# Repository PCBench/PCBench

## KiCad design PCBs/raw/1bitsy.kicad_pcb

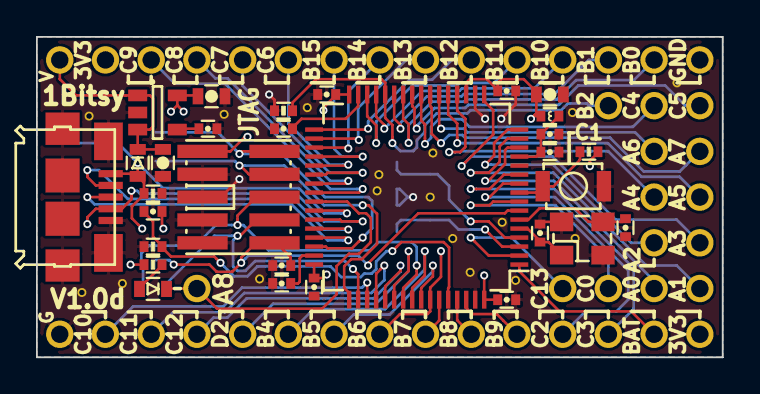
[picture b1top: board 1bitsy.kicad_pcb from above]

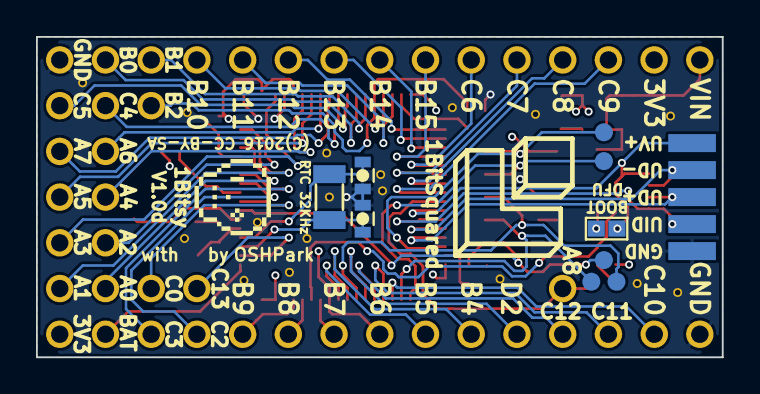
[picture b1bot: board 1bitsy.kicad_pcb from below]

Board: 2 copper layers, 38.1 x 17.8 mm, 88 parts (14 on the bottom side), 63 nets.

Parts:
C1, C5, C13: 4u7; C_0603
C2, C15: 1u; C_0402
C3: 470p; C_0402
C4, C10, C11, C12, C14, C18: 100n; C_0402
C6, C7: 10p; C_0603
C8, C9: 10p; C_0402
C16, C17: 2u2; C_0402
D1: >100mA; D_0603
J1: BOOT; J_0603
L1: 600 Ferrite; L_0402
LED1: ORA; D_0603
P1, P2, P3, P4, P5, P6, P7, P8, P9, P10, P11, P12, P13, P14, P15, P16, P17, P18, P19, P20, P21, P22, P23, P25, P26, P27, P28, P29, P30, P31, P32, P33, P34, P35, P36, P37, P38, P39, P40, P41, P42, P53, P54, P55: CONN_01X01; Pin_Header_Straight_Round_1x01
P24: USB_OTG; Connector_USB_Micro_B_SMD
P43, P44, P45, P46, P47: TP; POGO_PAD_SMD_R_1x1
P48, P49, P50, P51, P52: CONN_01X01; PAD_SMD_1x2.65
R1, R2, R3, R5: 10k; R_0402
R4: 300; R_0402
SW1: TACT; Tact_Switch_Top_B3U-1000P
U1: VREG_3V3; SOT-23-5
U2: STM32F415RGT; LQFP-64_10x10mm_Pitch0.5mm
X1: 32.768kHz; ABS07
X2: 25MHz; ABM8
X3: JTAG-10; FTSH-105-XX-X-DV

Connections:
+3V3: C5.1, C10.1, C11.1, C12.1, C13.1, C14.1, L1.1, P42.1, P54.1, R4.1, R5.1, U1.5, U2.19, U2.32, U2.48, U2.64, X3.1
/BOOT0: C15.2, R3.1, U2.60
/BUTTON: R5.2, SW1.2, U2.9
/JTAG_RST: C18.1, P47.1, U2.7, X3.10
/JTAG_TCK: P44.1, U2.49, X3.4
/JTAG_TDI: P46.1, U2.50, X3.8
/JTAG_TDO: P45.1, U2.55, X3.6
/JTAG_TMS: P43.1, U2.46, X3.2
/OSC32_IN: C6.2, U2.3, X1.2
/OSC32_OUT: C7.2, U2.4, X1.1
/OSC_IN: C8.2, U2.5, X2.1
/OSC_OUT: C9.2, U2.6, X2.2
/PA0: P1.1, U2.14
/PA1: P2.1, U2.15
/PA2: P3.1, U2.16
/PA3: P4.1, U2.17
/PA4: P5.1, U2.20
/PA5: P6.1, U2.21
/PA6: P7.1, U2.22
/PA7: P8.1, U2.23
/PA8: LED1.C, P9.1, U2.41
/PB0: P25.1, U2.26
/PB1: P26.1, U2.27
/PB2: P27.1, R2.1, U2.28
/PB4: P28.1, U2.56
/PB5: P29.1, U2.57
/PB6: P30.1, U2.58
/PB7: P31.1, U2.59
/PB8: P32.1, U2.61
/PB9: P33.1, U2.62
/PB10: P34.1, U2.29
/PB11: P35.1, U2.30
/PB12: P36.1, U2.33
/PB13: P37.1, U2.34
/PB14: P38.1, U2.35
/PB15: P39.1, U2.36
/PC0: P10.1, U2.8
/PC2: P12.1, U2.10
/PC3: P13.1, U2.11
/PC4: P14.1, U2.24
/PC5: P15.1, U2.25
/PC6: P16.1, U2.37
/PC7: P17.1, U2.38
/PC8: P18.1, U2.39
/PC9: P19.1, U2.40
/PC10: P20.1, U2.51
/PC11: P21.1, U2.52
/PC12: P22.1, U2.53
/PC13: P23.1, U2.2
/PD2: P11.1, U2.54
/USB_D+: P24.3, P50.1, U2.45
/USB_D-: P24.2, P49.1, U2.44
/USB_ID: P24.4, P51.1, U2.43
/USB_VBUS: D1.A, J1.1, P24.1, P48.1, R1.1, U2.42
/VBAT: P53.1, U2.1
/VIN: C1.1, D1.C, P40.1, U1.1, U1.3
GND: C1.2, C2.2, C3.2, C4.2, C5.2, C6.1, C7.1, C8.1, C9.1, C10.2, C11.2, C12.2, C13.2, C14.2, C16.2, C17.2, C18.2, P24.5, P24.GND, P41.1, P52.1, P55.1, R1.2, R2.2, R3.2, SW1.1, U1.2, U2.12, U2.18, U2.63, X2.GND, X3.3, X3.5, X3.7, X3.9
unnamed: C2.1, C4.1, L1.2, U2.13
unnamed: C3.1, U1.4
unnamed: C15.1, J1.2
unnamed: C16.1, U2.47
unnamed: C17.1, U2.31
unnamed: LED1.A, R4.2

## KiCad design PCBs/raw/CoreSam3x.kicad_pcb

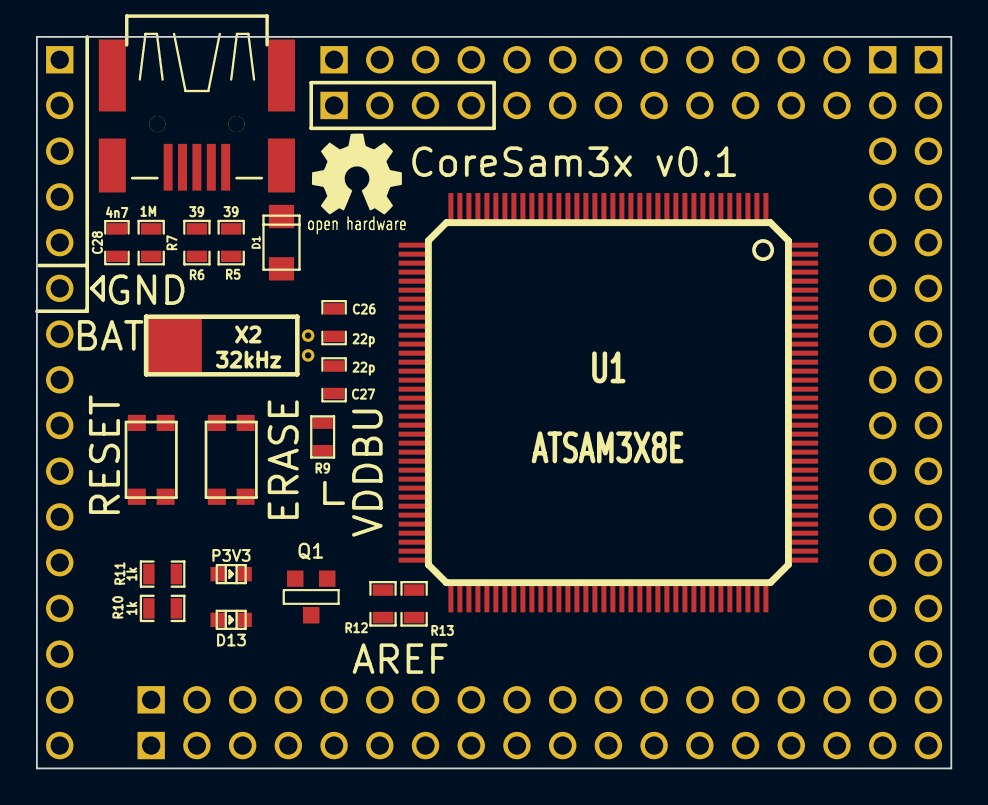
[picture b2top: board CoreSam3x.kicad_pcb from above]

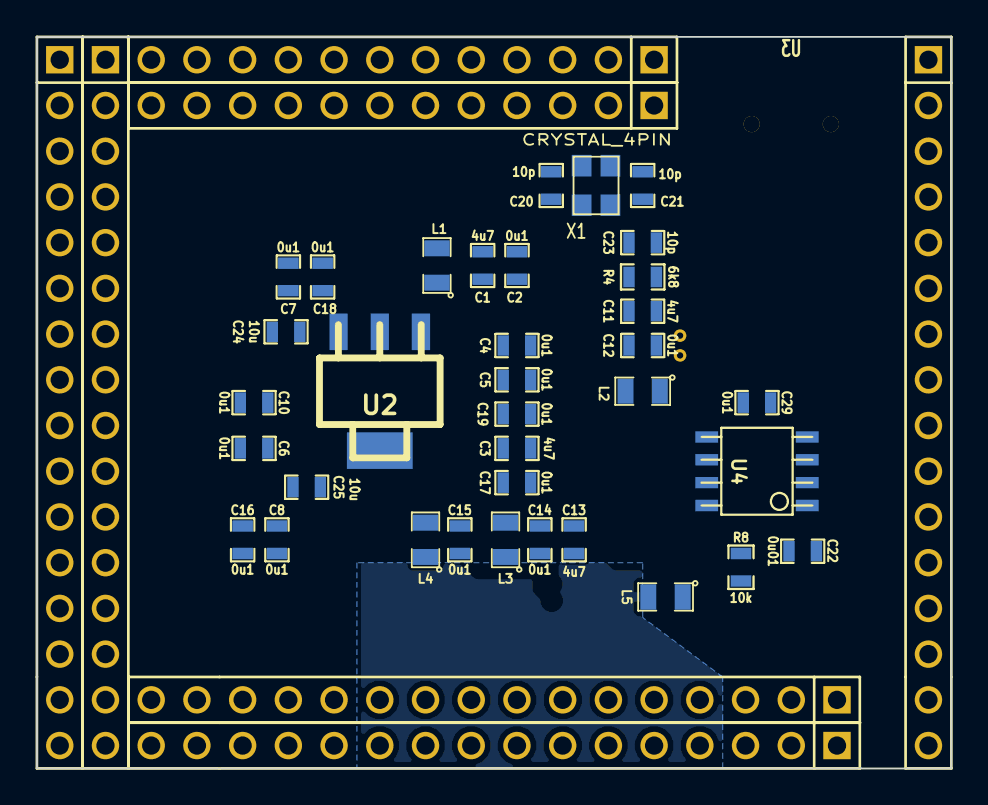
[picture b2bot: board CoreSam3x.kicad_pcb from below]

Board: 2 copper layers, 50.8 x 40.6 mm, 64 parts (42 on the bottom side), 128 nets, no tracks yet.

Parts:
C1, C3, C11, C13: 4u7; SM0603_Capa
C2, C4, C5, C6, C7, C8, C10, C12, C14, C15, C16, C17, C18, C19, C29: 0u1; SM0603_Capa
C20, C21, C23: 10p; SM0603_Capa
C22: 0u01; SM0603_Capa
C24, C25: 10u; SM0603_Capa
C26, C27: 22p; SM0603_Capa
C28: 4n7; SM0603_Capa
D1: DIODE; do219ab
D2: D13; Led_0603
D3: P3V3; Led_0603
L1, L2, L3, L4, L5: 100Mhz; SM0805
M1: PCB_GREEN_RMC; PCB_GREEN
M2: LOGO_OSHW; Logo_silk_OSHW_6x6mm
P1, P2: HDR; PIN_ARRAY_12x1_RMC
P3, P4, P5, P6, P8: HDR; PIN_ARRAY_16x1_RMC
Q1: BSS123; SOT23GDS
R4: 6k8; SM0603_Resistor
R5, R6: 39; SM0603_Resistor
R7: 1M; SM0603_Resistor
R8: 10k; SM0603_Resistor
R9: 0R; SM0603
R10, R11: 1k; SM0603_Resistor
R12, R13: 0R; SM0603_Resistor
S1: ERASE; SW_C&K_KMR4
S2: RESET; SW_C&K_KMR4
U1: ATSAM3X8E; LQFP144
U2: LM1117MP-3.3; SOT-223
U3: USBCONN-HOSTCAPABLE; CONN_MiniAB_SMT_RMC
U4: SP2525A-1EN; SOIC-8
X1: CRYSTAL_4PIN; XTAL-3.2x2.5mm
X2: 32kHz; crystal_tc-38_horiz_RMC

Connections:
+3.3V: C10.1, C16.1, C17.1, C18.1, C19.1, C22.1, C25.1, L2.2, L3.2, L4.2, P3.10, R9.1, R10.1, R11.1, S1.2, U1.11, U1.57, U1.62, U1.105, U1.125, U2.2, U2.4
+5V: C24.1, C29.1, D1.1, P3.4, U2.3, U4.5, U4.7
/Processor/UFAULT: U1.25, U4.2
/Processor/VDDCORE: C3.1, C4.1, C5.1, C6.1, C7.1, C8.1, L1.1, U1.10, U1.45, U1.56, U1.61, U1.104, U1.124
/Processor/VDDPLL: C1.1, C2.1, L1.2, U1.34
A0: P6.5, U1.78
A1: P5.6, U1.79
A2: P6.6, U1.80
A3: P5.7, U1.81
A4: P6.7, U1.82
A5: P5.8, U1.83
A6: P6.8, U1.84
A7: P5.9, U1.85
A8: P6.9, U1.88
A9: P5.10, U1.89
A10: P6.10, U1.90
A11: P5.11, U1.91
ADVREF: R12.2, R13.2, U1.75
CANRX0: P1.3, U1.24
CANTX0: P1.4, U1.23
CANTX1: P4.3, U1.140
D20_SDA: P6.11, U1.86
D21_SCL: P6.12, U1.87
D22: P4.2, U1.1
D23: P8.2, U1.7
D24: P2.10, U1.8
D25: P2.9, U1.13
D26: P1.9, U1.14
D27: P2.8, U1.15
D28: P1.8, U1.16
D29: P1.6, U1.19
D30: P2.5, U1.22
D31: P1.2, U1.26
D32: P1.1, U1.32
D33: P3.11, U1.55
D34: P3.12, U1.59
D35: P3.13, U1.60
D36: P8.12, U1.116
D37: P3.14, U1.63
D38: P3.15, U1.64
D39: P3.16, U1.65
D40: P6.1, U1.66
D41: P5.1, U1.67
D42: P5.3, U1.71
D43: P6.3, U1.72
D44: P4.16, U1.101
D45: P8.16, U1.100
D46: P5.15, U1.99
D47: P6.15, U1.98
D48: P5.14, U1.97
D49: P6.14, U1.96
D50: P5.13, U1.95
D51: P6.13, U1.94
D52_SS: P5.12, U1.92
D70_SDA1: P1.10, U1.9
D71_SCL1: P6.2, U1.70
DAC0_CANRX1: P6.4, U1.76
DAC1: P5.5, U1.77
DFSDM: R6.2, U1.43
DFSDP: R5.2, U1.42
DHSDM: R6.1, U1.38, U3.2
DHSDP: R5.1, U1.37, U3.3
ENET_CRSDV: P8.10, U1.119
ENET_MDC: P8.8, U1.123
ENET_MDIO: P4.8, U1.127
ENET_REF_CLK: P4.13, U1.113
ENET_RXD0: P4.10, U1.120
ENET_RXD1: P8.9, U1.121
ENET_RX_ER: P4.9, U1.122
ENET_TXD0: P4.12, U1.115
ENET_TXD1: P4.11, U1.118
ENET_TX_EN: P8.13, U1.114
ERASE: P3.5, S1.1, U1.130
EXTVREF: P5.4, R12.1
FWUP: P3.9, U1.53
GND: C1.2, C2.2, C3.2, C4.2, C5.2, C6.2, C7.2, C8.2, C10.2, C11.2, C12.2, C13.2, C14.2, C15.2, C16.2, C17.2, C18.2, C19.2, C20.2, C21.2, C23.2, C24.2, C25.2, C26.2, C27.2, C28.2, C29.2, D3.2, L5.1, P3.6, Q1.S, R4.2, R7.1, R8.1, S2.1, U1.12, U1.33, U1.44, U1.46, U1.51, U1.54, U1.58, U1.106, U1.126, U2.1, U3.4, U4.3, X1.2, X1.4
JTCK_SWCLK: P2.2, U1.28
JTDI: P2.4, U1.29
JTDO_SWO: P2.3, U1.30
JTMS_SWIO: P2.1, U1.31
unnamed: D2.1, R10.2
unnamed: D2.2, Q1.D
unnamed: C15.1, L4.1, R13.1
unnamed: D3.1, R11.2
unnamed: C28.1, R7.2, U3.5
unnamed: C21.1, U1.36, X1.1
unnamed: C23.1, R4.1, U1.40
unnamed: C20.1, U1.35, X1.3
unnamed: C26.1, U1.48, X2.1
unnamed: C27.1, U1.49, X2.2
PB24: P8.3, U1.143
PC10: P5.16, U1.117
PC11: P8.11, U1.93
PC20: P2.12, U1.131
PC27: P1.12, U1.138
PC30: P6.16, U1.103
PWM2: P8.4, U1.144
PWM3: P4.4, U1.139
PWM4_SS1: P8.5, U1.112, U1.137
PWM5: P4.5, U1.136
PWM6: P8.6, U1.135
PWM7: P4.6, U1.134
PWM8: P8.7, U1.133
PWM9: P4.7, U1.132
PWM10_SS0: P8.14, U1.102, U1.111
PWM11: P2.6, U1.20
PWM12: P1.5, U1.21
PWM13: P5.2, Q1.G, U1.68
RESET: C22.2, P3.1, S2.2, U1.47
RX0: P3.3, U1.27
RX1: P8.1, U1.3
RX2: P2.11, U1.5
RX3: P2.7, U1.18
SHDN: P3.8, U1.50
SPI0_MISO: P8.15, U1.108
SPI0_MOSI: P4.15, U1.109
SPI0_SPCK: P4.14, U1.110
TX0: P3.2, U1.2
TX1: P4.1, U1.4
TX2: P1.11, U1.6
TX3: P1.7, U1.17
UOTGID: U1.129, U3.6
UOTGVBOF: R8.2, U1.128, U4.1
VBUS: D1.2, U1.39, U3.1, U4.6, U4.8
VDDANA: C13.1, C14.1, L3.1, U1.73
VDDBU: P3.7, R9.2, U1.52
VDDUTMI: C11.1, C12.1, L2.1, U1.41
VSSA: L5.2, U1.74

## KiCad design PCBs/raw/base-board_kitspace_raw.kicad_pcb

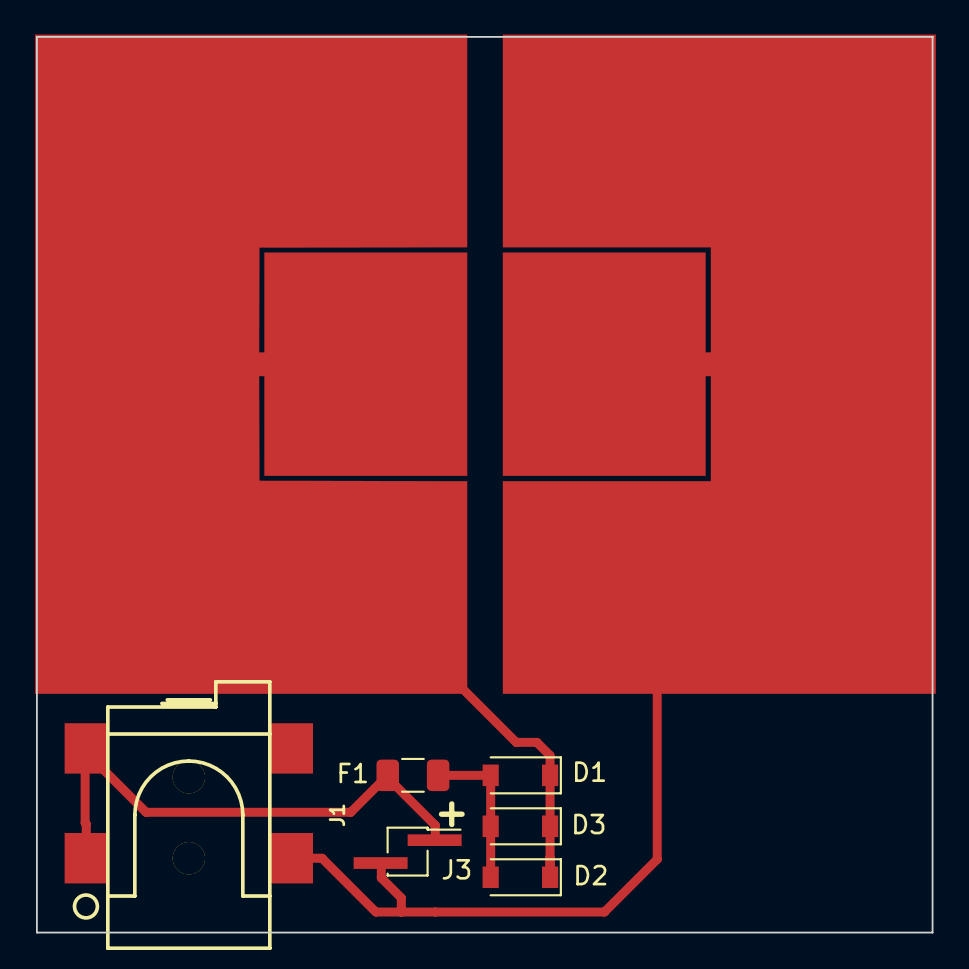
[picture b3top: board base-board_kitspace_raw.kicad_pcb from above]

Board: 2 copper layers, 49.8 x 49.8 mm, 7 parts (0 on the bottom side), 4 nets.

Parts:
D1, D2, D3: D; D_SOD-123
F1: Polyfuse; Fuse_1206_3216Metric
J1: Barrel_Jack_MountingPin; CUI-PJ-002AH-SMT_dc-barrel-jack
J2: Conn_01x01_Female; base_outline
J3: Conn_01x02_Male; PinHeader_1x02_P1.27mm_Vertical_SMD_Pin1Right

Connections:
+: D1.1, D2.1, D3.1
-: J1.2, J3.2
unnamed: D1.2, D2.2, D3.2, F1.1
unnamed: F1.2, J1.1, J3.1

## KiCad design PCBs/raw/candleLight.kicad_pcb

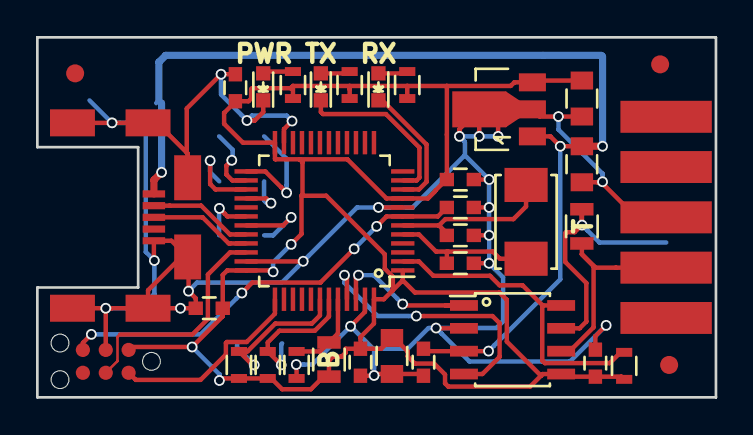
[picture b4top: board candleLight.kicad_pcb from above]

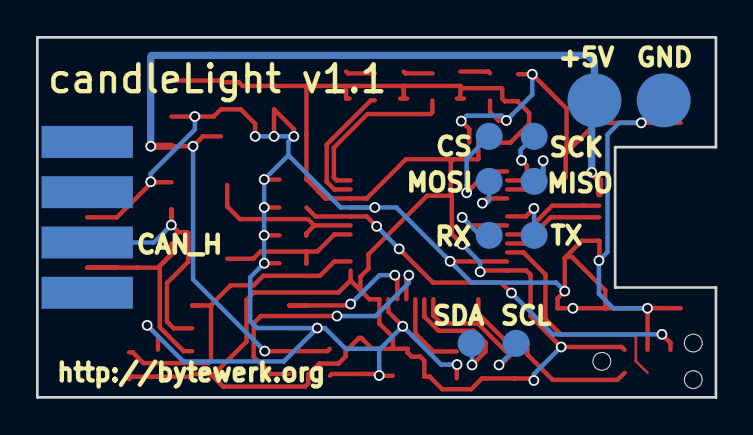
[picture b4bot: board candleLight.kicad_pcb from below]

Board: 2 copper layers, 37.7 x 20.0 mm, 44 parts (10 on the bottom side), 29 nets.

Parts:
C201, C202: 20pF; C_0603
C203, C204, C205, C206, C208, C402, C403: 100nF; C_0603
C207, C301, C303: 10uF; C_0805
CS: TEST_1P; Measurement_Point_Round-SMD-Pad_Small
D601, D602, D603: LED; LED_0603
FID101, FID102, FID103: Dummy_FIDUCIAL_Passermarke_Type1_RevE_Date16Nov20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; Fiducial_1mm_Dia_2.54mm_Outer_CopperTop
MISO: TEST_1P; Measurement_Point_Round-SMD-Pad_Small
MOSI: TEST_1P; Measurement_Point_Round-SMD-Pad_Small
P501: USB_OTG; Molex-Micro-USB-B-Middle-Mount
R201, R202: 4K7; R_0603
R203: R; R_0805
R204, R601, R602, R603: 1K; R_0603
R401: 10K; R_0603
R402: dnp; R_0805
RX: TEST_1P; Measurement_Point_Round-SMD-Pad_Small
SCK: TEST_1P; Measurement_Point_Round-SMD-Pad_Small
SCL: TEST_1P; Measurement_Point_Round-SMD-Pad_Small
SDA: TEST_1P; Measurement_Point_Round-SMD-Pad_Small
TX: TEST_1P; Measurement_Point_Round-SMD-Pad_Small
U201: STM32F072C8Tx; LQFP-48_7x7mm_Pitch0.5mm
U301: MCP1754ST-3302E/MB; SOT89-3_Housing
U401: TJA1051/3; SOIC-8_3.9x4.9mm_Pitch1.27mm
W301, W302: TEST_1P; Measurement_Point_Round-SMD-Pad_Big
X501: CON_SWD; TC2030-NL
X502: SUB-D9; DB9M_CI
Y201: 8MHz; ABM3

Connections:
+3V3: C203.1, C204.1, C205.1, C206.1, C207.1, C303.1, C403.1, R201.1, R202.2, R203.1, R401.1, R601.2, R602.2, R603.2, U201.1, U201.9, U201.24, U201.36, U201.48, U301.3, U401.5, X501.1
+5V: C301.1, C402.1, P501.1, U301.1, U401.3, W301.1
/CAN/CAN_H: R402.1, U401.7, X502.7
/CAN/CAN_L: R402.2, U401.6, X502.2
/CAN/CAN_S: R401.2, U201.2, U401.8
/Connectors/NRST: C208.1, U201.7, X501.5
/Connectors/SWCLK: U201.37, X501.2
/Connectors/SWDIO: U201.34, X501.4
/Connectors/USB_DM: P501.2, U201.32
/Connectors/USB_DP: P501.3, U201.33
/LEDs/LED1: D601.1, U201.10
/LEDs/LED2: D602.1, U201.11
/MCU/BOOT0: R203.2, R204.2, U201.44
/MCU/CAN_RX: U201.45, U401.4
/MCU/CAN_TX: U201.46, U401.1
GND: C201.1, C202.1, C203.2, C204.2, C205.2, C206.2, C207.2, C208.2, C301.2, C303.2, C402.2, C403.2, D603.1, P501.5, P501.6, R204.1, U201.8, U201.23, U201.35, U201.47, U301.2, U401.2, W302.1, X501.3, X502.3
unnamed: C201.2, U201.5, Y201.1
unnamed: C202.2, U201.6, Y201.2
unnamed: D601.2, R601.1
unnamed: D602.2, R602.1
unnamed: D603.2, R603.1
unnamed: R201.2, SCL.1, U201.42
unnamed: R202.1, SDA.1, U201.43
unnamed: CS.1, U201.25
unnamed: SCK.1, U201.26
unnamed: MISO.1, U201.27
unnamed: MOSI.1, U201.28
unnamed: TX.1, U201.30
unnamed: RX.1, U201.31

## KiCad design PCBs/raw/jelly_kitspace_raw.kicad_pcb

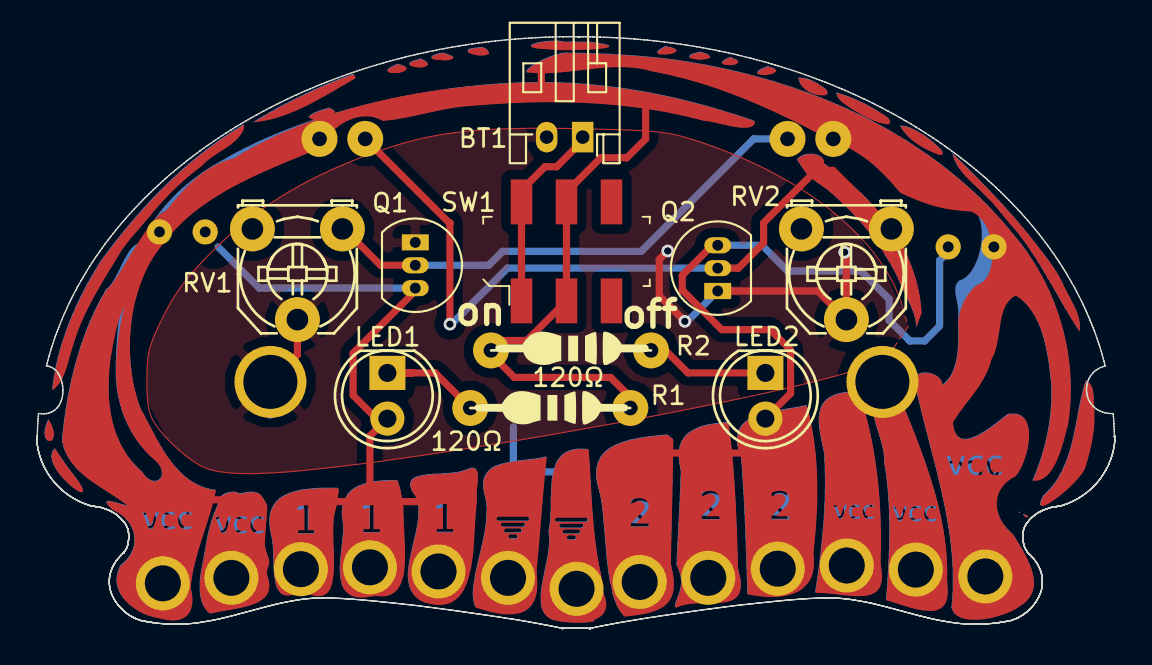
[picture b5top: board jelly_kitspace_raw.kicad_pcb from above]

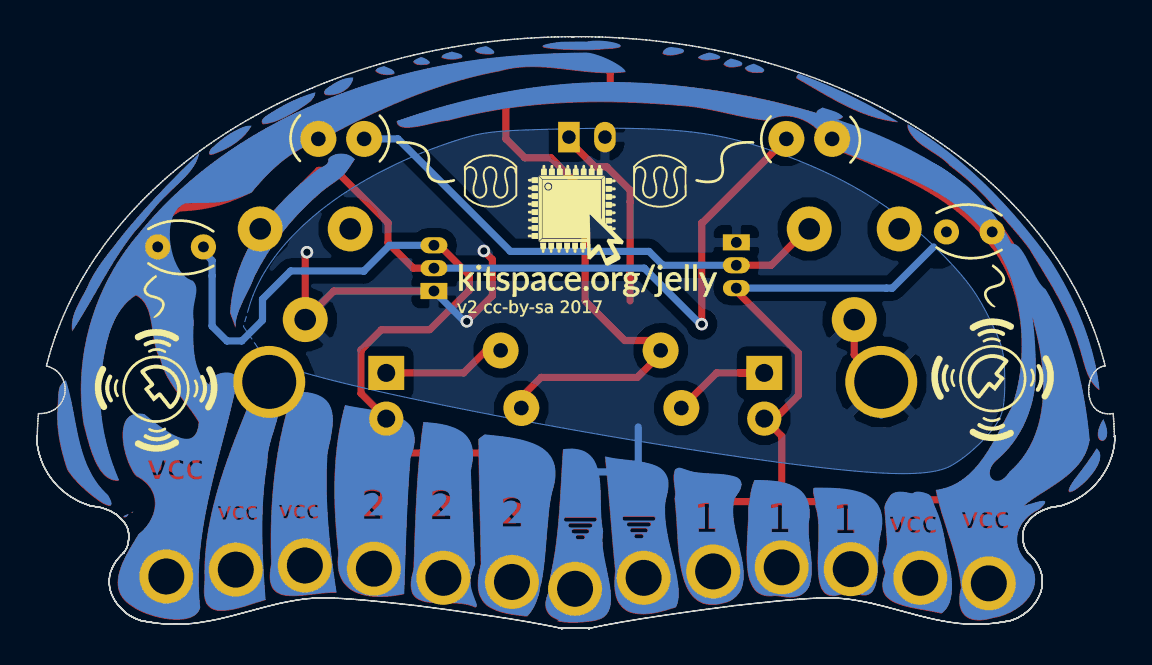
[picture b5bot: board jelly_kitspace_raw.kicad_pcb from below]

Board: 2 copper layers, 59.9 x 32.9 mm, 39 parts (5 on the bottom side), 9 nets.

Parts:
BT1: BATTERY; JST_PH_S2B-PH-K_02x2.00mm_Angled
DNP1: jelly
DNP2: ldr_image
DNP3: ldr_image; ldr_image_flipped
DNP4: logo
DNP5: name
DNP6: resistor_R1; resistor
DNP7: resistor_R2; resistor
DNP8: jelly_mirrored
DNP10: pager_motor_image1; page_motor_image
DNP11: pager_motor_image2; page_motor_image_flipped
LED1, LED2: LED; LED-5MM
M1, M2: PAGER_MOTOR; pager_motor_custom
P1, P2: CONN_01X01; hole
P3, P4, P5, P6, P7, P8, P9, P10, P11, P12, P13, P14, P15: CONN_01X01; hole2
PHOTO1, PHOTO2: Photores; ldr
Q1, Q2: Q_NMOS_SGD; TO-92_Inline_Narrow_Oval
R1, R2: 120Ω; R3-5
RV1, RV2: POT; Potentiometer_Triwood_RM-065
SW1: JS202011SCQN

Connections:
GND: BT1.2, P1.1, P8.1, P9.1, Q1.1, Q2.1, RV1.2, RV2.2
unnamed: BT1.1, SW1.1, SW1.4
unnamed: LED1.1, R1.1
unnamed: LED2.1, R2.1
unnamed: PHOTO1.1, Q1.2, RV1.1
unnamed: PHOTO2.1, Q2.2, RV2.1
VCC: M1.1, M2.1, P2.1, P3.1, P4.1, P13.1, P14.1, P15.1, PHOTO1.2, PHOTO2.2, R1.2, R2.2, SW1.2, SW1.5
Vout1: LED1.2, M2.2, P5.1, P6.1, P7.1, Q1.3
Vout2: LED2.2, M1.2, P10.1, P11.1, P12.1, Q2.3

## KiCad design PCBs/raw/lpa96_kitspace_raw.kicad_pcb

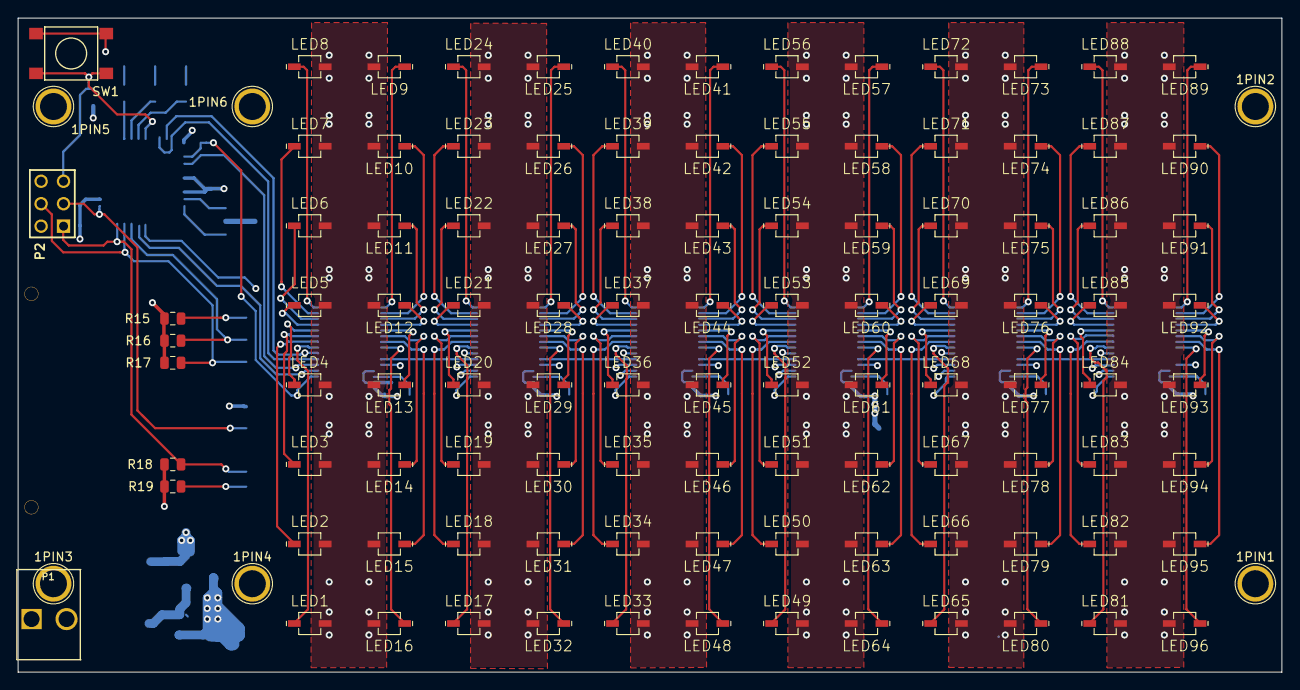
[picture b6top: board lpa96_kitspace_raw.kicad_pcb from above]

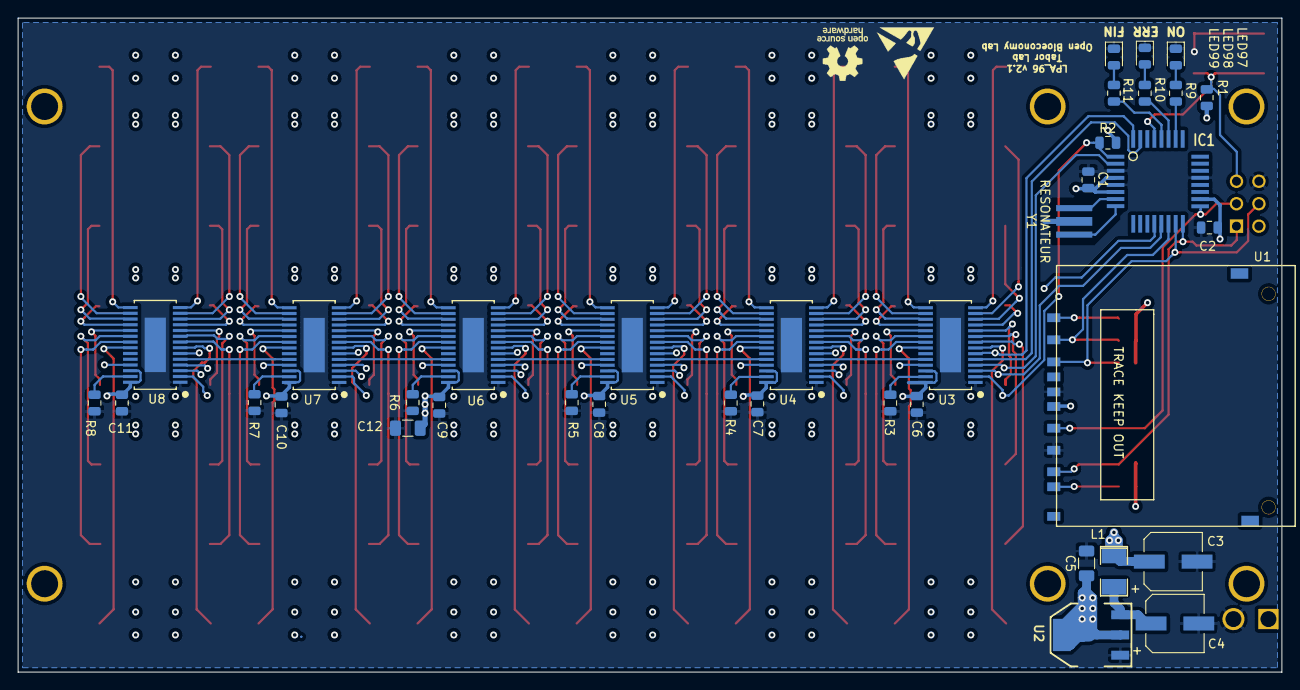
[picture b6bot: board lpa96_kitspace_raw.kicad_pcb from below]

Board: 4 copper layers, 143.0 x 74.0 mm, 147 parts (37 on the bottom side), 132 nets.

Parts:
1PIN1, 1PIN2, 1PIN3, 1PIN4, 1PIN5, 1PIN6: P***; 1pin
C1, C2, C6, C7, C8, C9, C10, C11: 100nF; C_0805_2012Metric
C3, C4: 47uF; CP_Elec_6.3x5.3
C5, C12: 10uF; C_1206_3216Metric
IC1: ATMEGA328-A; TQFP32_FIXED
L1: 10uH; L-1210
LED1, LED2, LED3, LED4, LED5, LED6, LED7, LED8, LED9, LED10, LED11, LED12, LED13, LED14, LED15, LED16, LED17, LED18, LED19, LED20, LED21, LED22, LED23, LED24, LED25, LED26, LED27, LED28, LED29, LED30, LED31, LED32, LED33, LED34, LED35, LED36, LED37, LED38, LED39, LED40, LED41, LED42, LED43, LED44, LED45, LED46, LED47, LED48, LED49, LED50, LED51, LED52, LED53, LED54, LED55, LED56, LED57, LED58, LED59, LED60, LED61, LED62, LED63, LED64, LED65, LED66, LED67, LED68, LED69, LED70, LED71, LED72, LED73, LED74, LED75, LED76, LED77, LED78, LED79, LED80, LED81, LED82, LED83, LED84, LED85, LED86, LED87, LED88, LED89, LED90, LED91, LED92, LED93, LED94, LED95, LED96: LED_ALT; VLDx1232G
LED97, LED98, LED99: LED_ALT; LED_0805_2012Metric
P1: CONN_2; PIN_ARRAY_2X1_3960um
P2: CONN_3X2; pin_array_3x2
R1, R2: 10k; R_0805_2012Metric
R3, R4, R5, R6, R7, R8: 2.2k; R_0805_2012Metric
R9, R10, R11: 330R; R_0805_2012Metric
R15, R16, R17, R18, R19: 47k; R_0805_2012Metric
SW1: SW_PUSH; SW_PUSH_SMD
U1: SD_CARD; SD_CONN
U2: LD1117S33; SOT223
U3, U4, U5, U6, U7, U8: TLC5941; TLC5941_PWP_28
Y1: RESONATEUR; crystal_smd

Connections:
/BLANK: IC1.1, R2.1, U3.2, U4.2, U5.2, U6.2, U7.2, U8.2
/ERR: IC1.27, R10.1
/FIN: IC1.28, R11.1
/GSCLK: IC1.12, U3.25, U4.25, U5.25, U6.25, U7.25, U8.25
/MISO: IC1.16, P2.1, R18.2, U1.7
/MODE: IC1.32, U3.6, U4.6, U5.6, U6.6, U7.6, U8.6
/MOSI: IC1.15, P2.4, R17.2, U1.2
/ON: IC1.26, R9.1
/RST: IC1.29, P2.5, R1.1, SW1.1
/SCK: IC1.17, P2.3, U1.5
/SCLK: IC1.2, U3.4, U4.4, U5.4, U6.4, U7.4, U8.4
/SIN: IC1.31, U3.5
/SS: IC1.14, R16.2, U1.1
/VIN: C3.1, L1.1, LED1.2, LED2.2, LED3.2, LED4.2, LED5.2, LED6.2, LED7.2, LED8.2, LED9.2, LED10.2, LED11.2, LED12.2, LED13.2, LED14.2, LED15.2, LED16.2, LED17.2, LED18.2, LED19.2, LED20.2, LED21.2, LED22.2, LED23.2, LED24.2, LED25.2, LED26.2, LED27.2, LED28.2, LED29.2, LED30.2, LED31.2, LED32.2, LED33.2, LED34.2, LED35.2, LED36.2, LED37.2, LED38.2, LED39.2, LED40.2, LED41.2, LED42.2, LED43.2, LED44.2, LED45.2, LED46.2, LED47.2, LED48.2, LED49.2, LED50.2, LED51.2, LED52.2, LED53.2, LED54.2, LED55.2, LED56.2, LED57.2, LED58.2, LED59.2, LED60.2, LED61.2, LED62.2, LED63.2, LED64.2, LED65.2, LED66.2, LED67.2, LED68.2, LED69.2, LED70.2, LED71.2, LED72.2, LED73.2, LED74.2, LED75.2, LED76.2, LED77.2, LED78.2, LED79.2, LED80.2, LED81.2, LED82.2, LED83.2, LED84.2, LED85.2, LED86.2, LED87.2, LED88.2, LED89.2, LED90.2, LED91.2, LED92.2, LED93.2, LED94.2, LED95.2, LED96.2, P1.1
/XLAT: IC1.13, U3.3, U4.3, U5.3, U6.3, U7.3, U8.3
/lpa96_leds_drivers/SOUT1: U3.24, U4.5
/lpa96_leds_drivers/SOUT2: U4.24, U5.5
/lpa96_leds_drivers/SOUT3: U5.24, U6.5
/lpa96_leds_drivers/SOUT4: U6.24, U7.5
/lpa96_leds_drivers/SOUT5: U7.24, U8.5
GND: C1.1, C2.1, C3.2, C4.2, C5.2, C6.2, C7.2, C8.2, C9.2, C10.2, C11.2, C12.2, IC1.3, IC1.5, IC1.21, LED97.1, LED98.1, LED99.1, P1.2, P2.6, R3.1, R4.1, R5.1, R6.1, R7.1, R8.1, SW1.2, U1.3, U1.6, U2.1, U3.1, U3.29, U4.1, U4.29, U5.1, U5.29, U6.1, U6.29, U7.1, U7.29, U8.1, U8.29, Y1.2
unnamed: C4.1, L1.2, U2.3
unnamed: IC1.7, Y1.3
unnamed: IC1.8, Y1.1
unnamed: LED1.1, U3.7
unnamed: LED2.1, U3.8
unnamed: LED3.1, U3.9
unnamed: LED4.1, U3.10
unnamed: LED5.1, U3.11
unnamed: LED6.1, U3.12
unnamed: LED7.1, U3.13
unnamed: LED8.1, U3.14
unnamed: LED9.1, U3.15
unnamed: LED10.1, U3.16
unnamed: LED11.1, U3.17
unnamed: LED12.1, U3.18
unnamed: LED13.1, U3.19
unnamed: LED14.1, U3.20
unnamed: LED15.1, U3.21
unnamed: LED16.1, U3.22
unnamed: LED17.1, U4.7
unnamed: LED18.1, U4.8
unnamed: LED19.1, U4.9
unnamed: LED20.1, U4.10
unnamed: LED21.1, U4.11
unnamed: LED22.1, U4.12
unnamed: LED23.1, U4.13
unnamed: LED24.1, U4.14
unnamed: LED25.1, U4.15
unnamed: LED26.1, U4.16
unnamed: LED27.1, U4.17
unnamed: LED28.1, U4.18
unnamed: LED29.1, U4.19
unnamed: LED30.1, U4.20
unnamed: LED31.1, U4.21
unnamed: LED32.1, U4.22
unnamed: LED33.1, U5.7
unnamed: LED34.1, U5.8
unnamed: LED35.1, U5.9
unnamed: LED36.1, U5.10
unnamed: LED37.1, U5.11
unnamed: LED38.1, U5.12
unnamed: LED39.1, U5.13
unnamed: LED40.1, U5.14
unnamed: LED41.1, U5.15
unnamed: LED42.1, U5.16
unnamed: LED43.1, U5.17
unnamed: LED44.1, U5.18
unnamed: LED45.1, U5.19
unnamed: LED46.1, U5.20
unnamed: LED47.1, U5.21
unnamed: LED48.1, U5.22
unnamed: LED49.1, U6.7
unnamed: LED50.1, U6.8
unnamed: LED51.1, U6.9
unnamed: LED52.1, U6.10
unnamed: LED53.1, U6.11
unnamed: LED54.1, U6.12
unnamed: LED55.1, U6.13
unnamed: LED56.1, U6.14
unnamed: LED57.1, U6.15
unnamed: LED58.1, U6.16
unnamed: LED59.1, U6.17
unnamed: LED60.1, U6.18
unnamed: LED61.1, U6.19
unnamed: LED62.1, U6.20
unnamed: LED63.1, U6.21
unnamed: LED64.1, U6.22
unnamed: LED65.1, U7.7
unnamed: LED66.1, U7.8
unnamed: LED67.1, U7.9
unnamed: LED68.1, U7.10
unnamed: LED69.1, U7.11
unnamed: LED70.1, U7.12
unnamed: LED71.1, U7.13
unnamed: LED72.1, U7.14
unnamed: LED73.1, U7.15
unnamed: LED74.1, U7.16
unnamed: LED75.1, U7.17
unnamed: LED76.1, U7.18
unnamed: LED77.1, U7.19
unnamed: LED78.1, U7.20
unnamed: LED79.1, U7.21
unnamed: LED80.1, U7.22
unnamed: LED81.1, U8.7
unnamed: LED82.1, U8.8
unnamed: LED83.1, U8.9
unnamed: LED84.1, U8.10
unnamed: LED85.1, U8.11
unnamed: LED86.1, U8.12
unnamed: LED87.1, U8.13
unnamed: LED88.1, U8.14
unnamed: LED89.1, U8.15
unnamed: LED90.1, U8.16
unnamed: LED91.1, U8.17
unnamed: LED92.1, U8.18
unnamed: LED93.1, U8.19
unnamed: LED94.1, U8.20
unnamed: LED95.1, U8.21
unnamed: LED96.1, U8.22
unnamed: LED97.2, R9.2
unnamed: LED98.2, R10.2
unnamed: LED99.2, R11.2
unnamed: R3.2, U3.27
unnamed: R4.2, U4.27
unnamed: R5.2, U5.27
unnamed: R6.2, U6.27
unnamed: R7.2, U7.27
unnamed: R8.2, U8.27
unnamed: R15.2, U1.9
unnamed: R19.2, U1.8
VCC: C1.2, C2.2, C5.1, C6.1, C7.1, C8.1, C9.1, C10.1, C11.1, C12.1, IC1.4, IC1.6, IC1.18, P2.2, R1.2, R2.2, R15.1, R16.1, R17.1, R18.1, R19.1, U1.4, U2.2, U2.4, U3.26, U3.28, U4.26, U4.28, U5.26, U5.28, U6.26, U6.28, U7.26, U7.28, U8.26, U8.28

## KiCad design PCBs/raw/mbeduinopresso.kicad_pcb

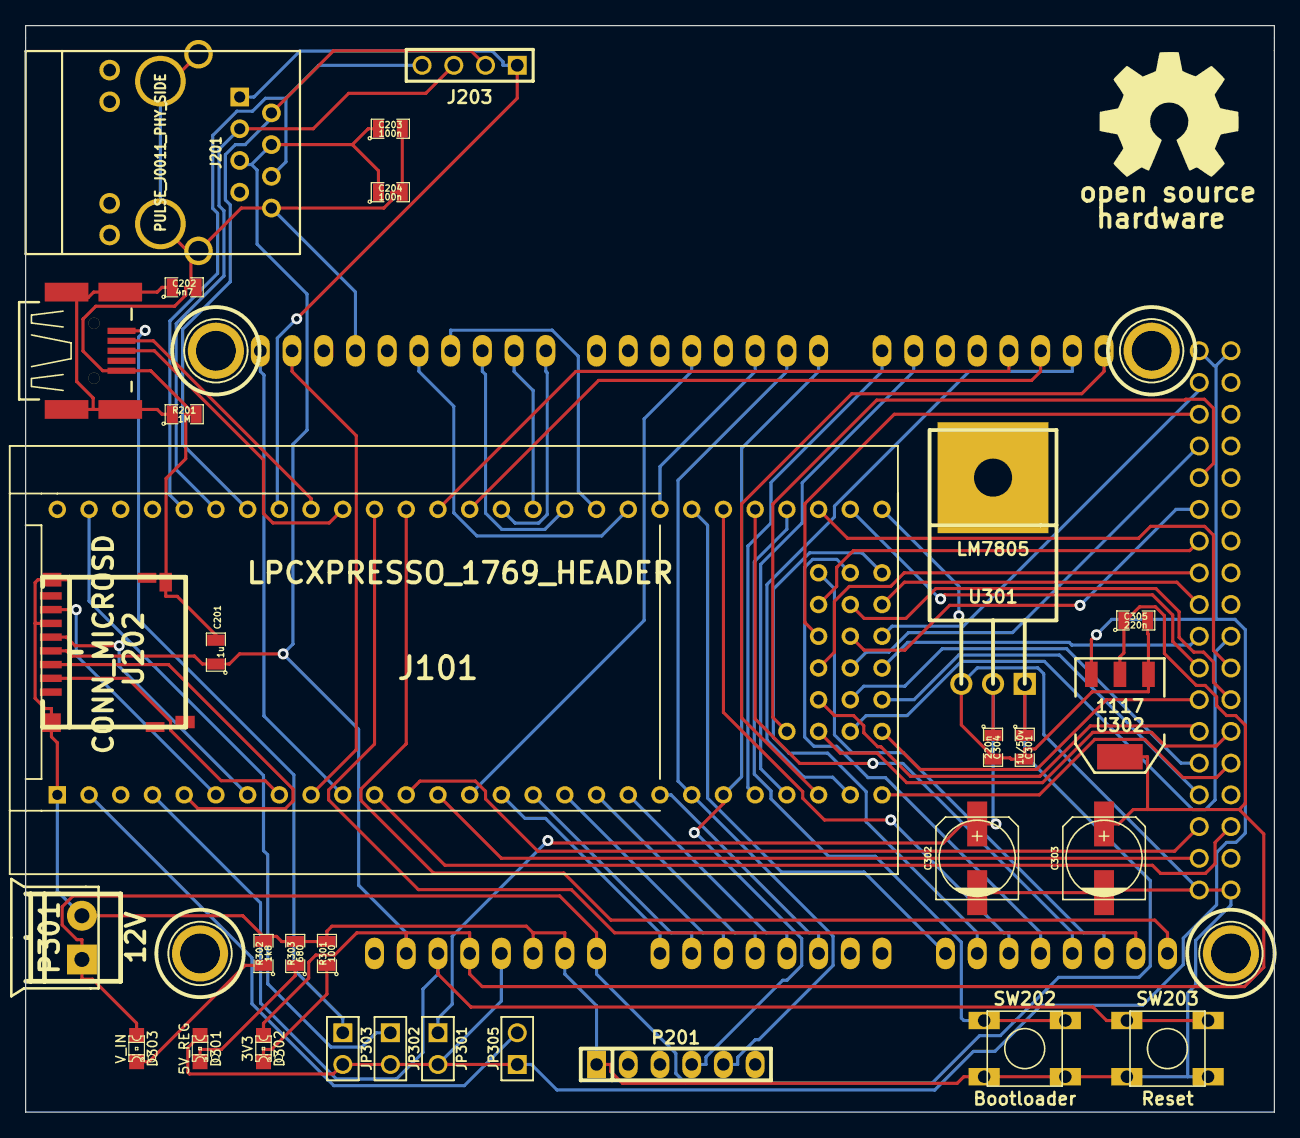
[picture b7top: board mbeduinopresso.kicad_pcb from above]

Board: 2 copper layers, 100.0 x 87.0 mm, 37 parts (0 on the bottom side), 77 nets.

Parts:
C201: 1u; SM0805
C202: 4n7; SM0805
C203, C204: 100n; SM0805
C301: 1u/50v; SM0805
C302, C303: 100u; c_elec_6.3x5.7
C304, C305: 220n; SM0805
D301: 5V_REG; LED-0805_GREEN
D302: 3V3; LED-0805_GREEN
D303: V_IN; LED-0805_GREEN
H201, H202, H203, H204: HOLE_RMC; HOLE_M3
J101: LPCXPRESSO_1769_HEADER; MBED_LPCXPRESSO
J201: PULSE_J0011_PHY_SIDE; RJ45_Halo_HFJ11
J203: Enet; PIN_ARRAY_4x1
JP301, JP302, JP303, JP305: JUMPER; PIN_ARRAY_2X1
M201: LOGO_OSHW; OSHW_logo_2
P201: SERIAL; pin_strip_6
P301: 12V; RMC-pt_1,5-2-3,5-h
R201: 1M; SM0805
R301: 100; SM0805
R302: 1k8; SM0805
R303: 680; SM0805
SHIELD101: ARDUINO_DUE_SHIELD; ARDUINO_MEGA_DUE_SHIELD_FOOTPRINT_RMC
SW202: Bootloader; SW_6x6_MULTI
SW203: Reset; SW_6x6_MULTI
U201: USBCONN; CONN_MiniAB_SMT_RMC
U202: CONN_MICROSD; MICRO_SD_DM3D
U301: LM7805; TO220
U302: 1117; SOT223

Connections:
*Bootloader: J101.51, SW202.1
*ETH_RD+: J101.33, J201.3, J203.3
*ETH_RD-: J101.32, J201.6, J203.4
*ETH_TD+: J101.35, J201.1, J203.1
*ETH_TD-: J101.34, J201.2, J203.2
*RESET: J101.4, SHIELD101.RST, SW203.1
*RX: J101.22, P201.4, SHIELD101.0
*TX: J101.21, P201.5, SHIELD101.1
*USB-D+: J101.37, U201.3
*USB-D-: J101.36, U201.2
+3.3V: C201.1, C203.1, C204.1, C303.1, C305.1, D302.1, J201.4, J201.5, SHIELD101.3V3, SHIELD101.IORF, U202.4, U302.2, U302.4
+5V: D301.1, JP301.2, JP302.2, JP303.2, JP305.1, SHIELD101.5V, SHIELD101.5V_4, SHIELD101.5V_5, U302.3
/Power/5V_REG: C302.1, C304.1, JP301.1, U301.3
AD4: J101.19, SHIELD101.AD4
AD5: J101.20, SHIELD101.AD5
CS_1: J101.8, U202.2
E0-DIR: J101.119, SHIELD101.28
E0-EN: J101.116, SHIELD101.42
E0-STEP: J101.104, SHIELD101.36
E1-DIR: J101.52, SHIELD101.41
E1-EN: J101.117, SHIELD101.39
E1-STEP: J101.105, SHIELD101.43
E2-DIR: J101.27, SHIELD101.47
E2-EN: J101.118, SHIELD101.45
E2-STEP: J101.106, SHIELD101.32
ESTOP: J101.53, SHIELD101.40
GND: C201.2, C202.2, C203.2, C204.2, C301.2, C302.2, C303.2, C304.2, C305.2, J101.1, J101.54, J201.8, J201.13, P201.1, P301.2, R201.2, R301.2, R302.2, R303.2, SHIELD101.GND, SW202.2, SW203.2, U201.4, U202.6, U202.9, U202.11, U301.2, U302.1
LPC_VIN: J101.2, JP305.2
MISO_0: J101.12, SHIELD101.50
MISO_1: J101.6, U202.7
MOSI_0: J101.11, SHIELD101.51
MOSI_1: J101.5, U202.3
unnamed: C202.1, R201.1, U201.5
unnamed: D301.2, R303.1
unnamed: D302.2, R301.1
unnamed: D303.2, R302.1
P0.4: J101.38, SHIELD101.AD14
P0.5: J101.39, SHIELD101.AD15
P0.21: J101.23, SHIELD101.14
P0.22: J101.24, SHIELD101.15
POWER1: J101.42, SHIELD101.8
POWER2: J101.43, SHIELD101.9
POWER3: J101.44, SHIELD101.10
POWER4: J101.45, SHIELD101.11
POWER5: J101.46, SHIELD101.12
POWER6: J101.47, SHIELD101.2
RXD2_SCL2: J101.41, SHIELD101.19
RXD3_SCL1: J101.10, SHIELD101.SCL1
SCK_0: J101.13, SHIELD101.52
SCK_1: J101.7, U202.5
SCL0: J101.26, SHIELD101.20
SDA0: J101.25, SHIELD101.21
SSEL_0: J101.14, SHIELD101.4
THERM0: J101.15, SHIELD101.AD0
THERM1: J101.16, SHIELD101.AD1
THERM2: J101.17, SHIELD101.AD2
THERM3: J101.18, SHIELD101.AD3
TXD2_SDA2: J101.40, SHIELD101.18
TXD3_SDA1: J101.9, SHIELD101.SDA1
VIN: C301.1, D303.1, P301.1, SHIELD101.V_IN, U301.1
VUSB1: J101.29, JP302.1
VUSB2: JP303.1, U201.1
X-DIR: J101.48, SHIELD101.AD8
X-EN: J101.113, SHIELD101.48
X-STEP: J101.101, SHIELD101.AD9
XMAX: J101.108, SHIELD101.30
XMIN: J101.107, SHIELD101.22
Y-DIR: J101.49, SHIELD101.AD10
Y-EN: J101.114, SHIELD101.46
Y-STEP: J101.102, SHIELD101.AD11
YMAX: J101.110, SHIELD101.38
YMIN: J101.109, SHIELD101.24
Z-DIR: J101.50, SHIELD101.AD12
Z-EN: J101.115, SHIELD101.44
Z-STEP: J101.103, SHIELD101.AD13
ZMAX: J101.112, SHIELD101.34
ZMIN: J101.111, SHIELD101.26

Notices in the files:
PCBs/raw/1bitsy.kicad_pcb:
(C) 2016 Piotr Esden-Tempski
(C) 2016 1BitSquared LLC
License: CC-BY-SA V4.0
(C)2016 CC-BY-SA
